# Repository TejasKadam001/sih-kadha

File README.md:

# iKwath: Smart Pod-Based Ayurvedic Decoction Appliance

**SIH26048: iKwath, a pod-based smart Kwatha (Kadha) maker that prepares a fresh, AFI/API-standardized decoction from coarse powder (yavakuta churna) on demand, in the shortest practical time, without altering the decoction's quality or yield**
Ministry of Ayush / All India Institute of Ayurveda (AIIA) | Smart India Hackathon 2026
**Team:** MACH 2
**Design philosophy:** Classical Fidelity | Hardware-Enforced Safety | Measured Endpoints, Not Timers | Honest Project Status

[-lightgrey.svg?style=flat-square)](website/)

---

## 1. Problem Statement Context (SIH26048)

Kwatha (also Kashaya or Kadha) is the primary aqueous decoction in Ayurveda. Coarse herbal powder (yavakuta churna) is boiled in a specified multiple of water and reduced, classically to one quarter of the volume, then filtered immediately.

The difficulty is that a classical Kwatha has no preservatives and stays therapeutically useful for only a few hours. Making it properly means 45 to 60 minutes of monitored simmering, so patients and OPD clinics often switch to bottled, industrially preserved syrups that suffer thermal degradation or inconsistent yield.

* **Long manual process:** open-pot evaporation needs constant attention for close to an hour.
* **Temperature ceiling:** classical practice prescribes gentle heat (Manda Agni). At or above 100 C volatile terpenes and thermolabile glycosides degrade.
* **Standardization gap:** hand preparation varies in water ratio, reduction and filtration, so dose consistency is poor.
* **No traceability:** there is no record of what was brewed, from which batch, at what concentration.

---

## 2. Integrated Solution Overview

**iKwath** is a countertop, single-dose extraction appliance built around five ideas:

1. **Pod-based dosing:** a single-use pod holds 25 to 35 g of certified coarse powder and doubles as the filter (150 to 250 micron mesh). An NTAG213 NFC tag on the rim carries the formulation profile.
2. **Vacuum-assisted evaporation:** the sealed SS304 chamber runs at 0.5 to 0.6 atm so water boils at about 82 to 86 C. The liquid boils vigorously while staying inside the 85 to 90 C envelope.
3. **Measured endpoint:** a load cell tracks the mass of the chamber and ends the boil when 300 g (+/- 2 g) has evaporated, an exact 4:1 reduction of 400 mL. The endpoint is a measurement, not a timer.
4. **Three independent hardware safety layers:** fuse, lid interlock and bimetallic thermal cutoff, all working with the firmware switched off.
5. **Companion app and cloud model:** live brew dashboard, pod profile catalogue, dose log and clinic fleet view (see the status note in section 8).

> Scientific and engineering classification: iKwath is a prototype design for a standardized decoction appliance. It is not a certified medical device, and this repository does not contain laboratory validation of extract quality. See section 10 for what is and is not built.

---

## 3. Extraction Physics

The Ayurvedic Formulary of India (AFI) and Ayurvedic Pharmacopoeia of India (API) set water ratio by herb hardness:

| Herb class | Parts | Water ratio (w/w) | Reduction | Concentration |
|---|---|---|---|---|
| Soft (Mridu): leaves, flowers | 16 | 16 | to 1/4 | about 4x |
| Medium (Madhyama): bark, stems | 8 | 8 | to 1/4 | about 2x |
| Hard (Kathina): roots, heartwood | 4 | 4 | to 1/4 | about 1x |

The working profile is 400 mL of water reduced to a 100 mL dose.

Cycle time falls from 45 to 60 minutes to 9 to 12 minutes without raising liquid temperature, using four levers:

```mermaid
graph TD
    A[Classical bottleneck] --> B[Open pot at 98-100 C]
    B --> C[Slow evaporation: 45-60 min]
    B --> D[Thermal loss of volatile actives]

    E[iKwath approach] --> F[Sealed chamber at 0.5-0.6 atm]
    F --> G[Boils at 82-86 C, Manda Agni preserved]
    E --> H[Wide shallow pan: about 3x surface area]
    E --> I[Recirculation over the pod bed]
    E --> J[Forced vapor exhaust]

    G --> K[Active cycle target: 9-12 min]
    H --> K
    I --> K
    J --> K
```

Particle size follows PCIM&H specification AFI/2020/KC/1.0: 100 percent through IS sieve 22 (710 micron) and not more than 10 percent through sieve 44 (355 micron). Details: [docs/pod-and-extraction.md](docs/pod-and-extraction.md).

---

## 4. Machine Working Principle

```mermaid
stateDiagram-v2
    [*] --> Idle: Powered on
    Idle --> PodDetect: Pod inserted, lid latched
    PodDetect --> WaterFill: NFC profile validated
    WaterFill --> PreSoak: 400 mL metered by load cell
    PreSoak --> ActiveBoil: 180 s soak finished

    state ActiveBoil {
        [*] --> PressureRamp: Vacuum pump on
        PressureRamp --> PIDHold: 0.5-0.6 atm reached
        PIDHold --> PIDHold: Temperature held 85-88 C
        PIDHold --> MassCheck: Recirculation running
        MassCheck --> [*]: 300 g evaporated
    }

    ActiveBoil --> Dispense: Vent chamber, run dispense pump
    Dispense --> Eject: about 100 mL delivered
    Eject --> Idle: Pod dropped to bin
```

Eight steps: interlocked pod loading, metered water intake, pre-soak, controlled vacuum boil, recirculation with vapor stripping, mass-reduction endpoint, filtered dispense at 55 to 60 C, automatic pod ejection. Step-by-step detail: [docs/control-sequence.md](docs/control-sequence.md).

---

## 5. Repository Layout

```
SIH/
├── README.md                      Main specification and status
├── INSTALL.md                     How to open, run and rebuild each part
├── CHANGELOG.md                   Versioned release notes
├── PUSH_LOG.md                    What each push to the repository did
├── SIH26048_PROJECT_REPORT.md     Full technical submission report
├── ps_shortlist.md                Problem-statement shortlist and selection notes
├── app/                           Product landing site (single page, with media assets)
│   ├── index.html
│   ├── styles.css
│   ├── assets/                    Product, pod and lifestyle imagery, hero video
│   └── _assets_backup/            Unused media with a restore script
├── website/                       Interactive brew-simulator web app (HTML, CSS, JS)
│   ├── index.html
│   ├── styles.css
│   ├── app.js                     Screen state machine, extraction simulator, greetings
│   ├── manifest.json
│   └── assets/
├── pcb/                           Committed KiCad project (control and power circuitry)
│   ├── ikwath.kicad_sch
│   ├── ikwath.kicad_pcb
│   └── ikwath.kicad_pro
├── ino/                           ESP32 firmware (Arduino sketch)
│   └── ikwath_firmware/
│       ├── ikwath_firmware.ino    State machine, sensors, safety checks, serial and optional HTTP
│       ├── pins.h  config.h       Pin map and tunable settings
│       ├── pid.h  hx711_lite.h    Heater PID and load-cell reader
│       └── profile.h              Pod tag payload format
├── models/                        Process model notebook: vacuum boiling, energy budget, endpoint noise, pod tag
│   └── ikwath_process_model.ipynb
├── docs/                          Engineering documentation derived from this repository
│   ├── pod-and-extraction.md
│   ├── control-sequence.md
│   ├── pinout-and-buses.md
│   ├── safety-system.md
│   ├── pcb-status.md
│   ├── bom.md
│   ├── app-and-cloud.md
│   ├── limitations.md
│   ├── judge-qna.md
│   └── README.md
├── blehpcb/                       Local PCB generation work (gitignored)
│   ├── BOM.csv
│   ├── generate_final_kicad8.py
│   ├── ikwath-control-board/  ikwath-power-board/
│   ├── *-drc.rpt  *-erc.rpt       KiCad rule-check reports
│   └── pcbreal/                   Scripted placement, routing and stackup iterations
└── blehread/                      Local research dossiers (gitignored)
    ├── research.md  structure.md  pcb.md  app_and_website.md  names.md  open.md
```

The two gitignored folders are working material that lives only on the author's machine; see [PUSH_LOG.md](PUSH_LOG.md) for what is actually pushed.

---

## 6. Dual-PCB Hardware Architecture

The electronics are split into two boards so that sensitive analog measurement is isolated from inductive relay switching.

```mermaid
flowchart LR
    subgraph PB["Power Board"]
        AC["220V AC"] --> PS1["12V 5A AC-DC supply"]
        PS1 --> F1["5A DC fuse"]
        F1 --> V12["12V bus"]
        V12 --> BUCK["LM2596 buck to 5V"]
        V12 --> RLY["Relays 1-7: heater, vacuum pump, recirculation pump, dispense pump, inlet valve, lid lock, exhaust fan"]
    end

    subgraph CB["Control Board"]
        MCU["ESP32 DevKit V1"]
        MCU --> DS["DS18B20 liquid temperature"]
        MCU --> HX["HX711 + load cell"]
        MCU --> NFC["MFRC522 NFC reader"]
        MCU --> I2C["I2C bus"]
        I2C --> OLED["SSD1306 OLED"]
        I2C --> BMP["BMP280 pressure"]
        I2C --> PCF["PCF8574 x2: relays, LEDs"]
        MCU --> TDS["Analog TDS sensor"]
        MCU --> SW["Limit switches: lid, boil-over, level"]
        MCU --> SRV["SG90 pod ejector"]
    end

    BUCK -->|5V| MCU
    PB <-->|"Ribbon: power, I2C, PID, signals"| CB
```

| Board | Target size | Notes |
|---|---|---|
| Control | 70 x 60 mm in the specification (generated variants are larger, see [docs/pcb-status.md](docs/pcb-status.md)) | 2-layer, dedicated analog ground zone, 4x M3 |
| Power | 80 x 70 mm in the specification | 2-layer, heavy power traces, opto-isolated relay drive, 4x M3 |

Pin map and I2C addresses: [docs/pinout-and-buses.md](docs/pinout-and-buses.md).

---

## 7. Three-Tier Hardware Safety System

These layers act independently of firmware:

1. **Bimetallic thermal cutoff (95 to 100 C)**, in contact with the boiler wall and in series between Relay 1 and the heater. If the chamber overheats for any reason, including a welded relay, it opens the circuit.
2. **Mechanical lid interlock**, wired in series with the heater's 12 V feed. Opening the lid cuts heater power in hardware.
3. **5 A fast-acting fuse** on the 12 V rail against short circuits and pump stall.

The firmware in `ino/` adds supervisory checks on top (boil-over sensor, water level, enclosure NTC, over-temperature, timeouts); it is a first draft that has not yet run on the appliance (section 10). Details: [docs/safety-system.md](docs/safety-system.md).

---

## 8. Companion Applications

Two web front ends are in the repository. Both run with no build step and no dependencies.

| Folder | What it is |
|---|---|
| `website/` | Interactive mobile-style app: logo intro, login, time-based greeting, pod dropdown (Triphala, Ayush, Dashamoola), five-stage extraction simulator with live countdown, temperature dial, 400 to 100 mL gauge and a PID curve pinned to the 85 to 90 C band, notification bell, pod scanner viewfinder, profile view, Android frame toggle |
| `app/` | Single-page product site: appliance, pods, app, formulations, science and standards sections, sign-in and sign-up modals, product photography and hero video |

**Status:** the extraction screen is a simulator driven by `website/app.js`. It does not connect to a device. The BLE provisioning, local WebSocket, MQTT telemetry and cloud database described in [docs/app-and-cloud.md](docs/app-and-cloud.md) are the intended architecture, not running code.

---

## 9. Bill of Materials

`blehpcb/BOM.csv` lists 46 line items (ESP32, sensors, NFC reader, display, expanders, 7 relays, pumps, valves, heater, servo, fan, safety parts, passives and connectors). The file's own total row, and the sum of its cost column, is **INR 4,588** (about US$55), reading each figure as a line total. If those were unit prices the bill would be INR 8,335, so spot-check a few lines against supplier listings before quoting a cost. Full table and notes: [docs/bom.md](docs/bom.md).

---

## 10. Project Status: Built Versus Designed

| Area | Status |
|---|---|
| Problem analysis, extraction physics, pod design | Written (`blehread/research.md`, `docs/pod-and-extraction.md`) |
| Pin-by-pin hardware specification | Written (`blehread/pcb.md`, `docs/pinout-and-buses.md`) |
| KiCad schematic and PCB | Present in several iterations; `pcb/` is the committed one. Rule-check results vary by iteration, and copper routing is incomplete in some (see [docs/pcb-status.md](docs/pcb-status.md)) |
| Web front ends | Built and runnable; extraction is simulated |
| ESP32 firmware | Written (`ino/`): full cycle, safety checks, serial and optional HTTP interface. Not yet compiled here or run on hardware |
| Physical prototype and lab validation | **Not done** (no measured extract quality, no measured cycle time) |
| Mobile app, cloud backend, MQTT | **Design only** |

The 9 to 12 minute cycle, the 85 to 90 C envelope and the 300 g endpoint are design targets derived from the physics, not measured results. An energy balance in `models/ikwath_process_model.ipynb` shows that the cycle time is set by heater power: the 50 W element in the current bill of materials is far too small for a 12 minute cycle, so the heater is an open design decision. [docs/limitations.md](docs/limitations.md) lists what is needed to turn each into a measured claim.

---

## 11. Documentation Map

| Document | Contents |
|---|---|
| [SIH26048_PROJECT_REPORT.md](SIH26048_PROJECT_REPORT.md) | Full technical submission report |
| [INSTALL.md](INSTALL.md) | Run the web apps, open the PCB, regenerate boards |
| [CHANGELOG.md](CHANGELOG.md) | Versioned release notes |
| [PUSH_LOG.md](PUSH_LOG.md) | What each push did |
| [ino/README.md](ino/README.md) | Firmware structure, cycle, safety checks, serial commands |
| [docs/](docs/README.md) | Engineering documentation set |

---

## 12. Authoritative Standards and Citations

* PCIM&H, *AFI/2020/KC/1.0: Formulary Specification of AYUSH Kvatha Churna*, Ghaziabad.
* PCIM&H, *API-2/2020/KC/1.0: Pharmacopoeial Monograph of AYUSH Kvatha Churna*, Ministry of Ayush.
* *The Ayurvedic Pharmacopoeia of India*, Parts I and II, First Edition, Ministry of Health and Family Welfare / Ministry of Ayush.
* All India Institute of Ayurveda (AIIA): guidance on quality control, good dispensing practice and clinical standardization of extemporaneous decoctions.

---

*iKwath, Smart India Hackathon 2026, Ministry of Ayush / AIIA*
*Team: MACH 2*

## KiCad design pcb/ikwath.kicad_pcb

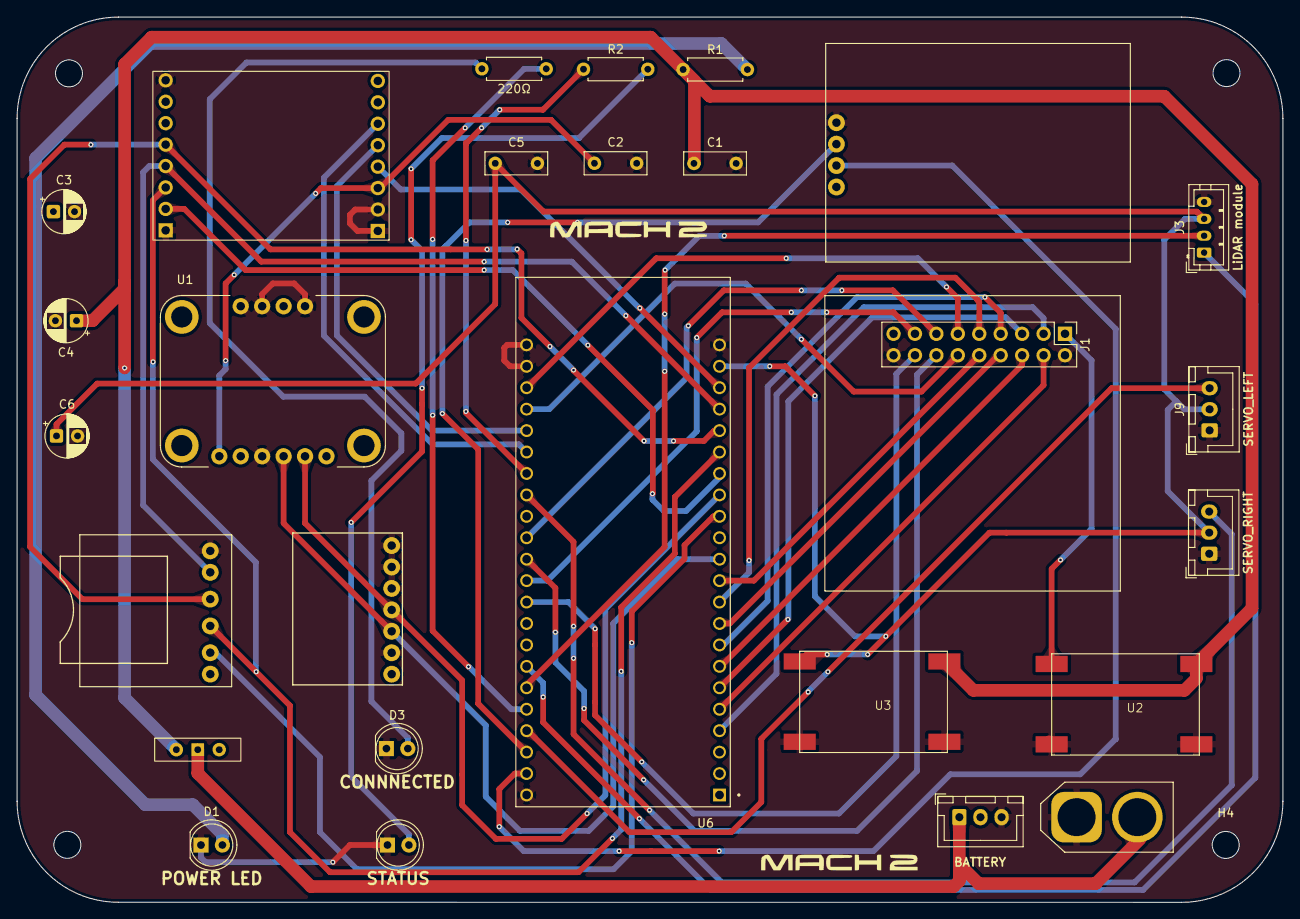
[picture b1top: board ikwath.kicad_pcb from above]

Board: 2 copper layers, 150.0 x 104.9 mm, 31 parts (0 on the bottom side), 40 nets.

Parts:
220Ω: 220Ω; R_Axial_DIN0207_L6.3mm_D2.5mm_P7.62mm_Horizontal
C1, C2, C5: 0.1µF; C_Rect_L7.2mm_W2.5mm_P5.00mm_FKS2_FKP2_MKS2_MKP2
C3, C6: 220; CP_Radial_D5.0mm_P2.50mm
C4: 470; CP_Radial_D5.0mm_P2.50mm
D1: POWER LED; LED_D5.0mm
D2: STATUS; LED_D5.0mm
D3: CONNNECTED; LED_D5.0mm
GPS1: NEO_GPS
H1, H2, H4, H6: MountingHole; MountingHole_3.2mm_M3_ISO7380
J1: CAMERA MODULE; PinHeader_2x09_P2.54mm_Vertical
J2: BATTERY; JST_XH_B3B-XH-A_1x03_P2.50mm_Vertical
J3: LiDAR module; JST_PH_B4B-PH-K_1x04_P2.00mm_Vertical
J5: XT-60; AMASS_XT60-M_1x02_P7.20mm_Vertical
J9: SERVO_LEFT; JST_XH_B3B-XH-A_1x03_P2.50mm_Vertical
J11: SERVO_RIGHT; JST_XH_B3B-XH-A_1x03_P2.50mm_Vertical
R1: 3.3KΩ; R_Axial_DIN0207_L6.3mm_D2.5mm_P7.62mm_Horizontal
R2: 220Ω; R_Axial_DIN0207_L6.3mm_D2.5mm_P7.62mm_Horizontal
SDMODULE1: sd_card_module
SW1: SW_Wuerth_450301014042; SW_Slide-03_Wuerth-WS-SLTV_10x2.5x6.4_P2.54mm
U1: BNO055; MODULE_2472
U2, U3: LM2596_buck_conv
U5: LORA_MODULE; SX1278 LoRa Module
U6: ESP32-S3-DEVKITC-1U-N8R2; XCVR_ESP32-S3-DEVKITC-1U-N8R2
m1: MS5611; MS5611F

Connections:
3.3V: C2.1, C3.1, GPS1.3V3, J1.1, SDMODULE1.3V3, U1.1 (VIN), U2.3 (VOUT+), U5.16 (VCC), m1.3.3V
5V: C5.1, C6.1, J3.3, J9.2, J11.2, U3.3 (VOUT+), U6.J1_21 (5V0)
GND: C1.2, C2.2, C3.2, C4.2, C5.2, C6.2, D1.1 (K), D2.1 (K), D3.1 (K), GPS1.GND, J1.2, J1.18, J2.3, J3.4, J5.1, J9.1, J11.1, SDMODULE1.GND, U1.3 (GND), U1.7 (ADR), U1.9 (PS1), U1.10 (PS0), U2.2 (VIN-), U2.4 (VOUT-), U3.2 (VIN-), U3.4 (VOUT-), U5.1 (GND), U5.13 (GND), U5.14 (GND), U5.15 (GND), U6.J1_22 (GND), U6.J3_1 (GND), U6.J3_21 (GND), U6.J3_22 (GND), m1.CSB, m1.GND, m1.PS, m1.SDO
GPIO1: J9.3, U6.J3_4 (GPIO1)
GPIO2: 220Ω.1, U6.J3_5 (GPIO2)
GPIO4: J1.3, U6.J1_4 (GPIO4)
GPIO5: J1.4, U6.J1_5 (GPIO5)
GPIO6: J1.5, U6.J1_6 (GPIO6)
GPIO7: J1.6, U6.J1_7 (GPIO7)
GPIO8: U1.4 (SDA), U6.J1_12 (GPIO8), m1.SCL
GPIO9: U1.5 (SCL), U6.J1_15 (GPIO9), m1.SDA
GPIO10: U5.5 (NSS), U6.J1_16 (GPIO10)
GPIO11: SDMODULE1.MOSI, U5.3 (MOSI), U6.J1_17 (GPIO11)
GPIO12: SDMODULE1.CLK, U5.4 (SCK), U6.J1_18 (GPIO12)
GPIO13: SDMODULE1.MISO, U5.2 (MISO), U6.J1_19 (GPIO13)
GPIO14: U5.6 (RESET), U6.J1_20 (GPIO14)
GPIO15: J1.7, U6.J1_8 (GPIO15)
GPIO16: J1.8, U6.J1_9 (GPIO16)
GPIO17: J1.9, U6.J1_10 (GPIO17)
GPIO18: J1.10, U6.J1_11 (GPIO18)
GPIO19: J1.11, U6.J3_20 (USB_D-/GPIO19)
GPIO20: J1.12, U6.J3_19 (USB_D+/GPIO20)
GPIO21: U5.7 (DI0O), U6.J3_18 (GPIO21)
GPIO35: J1.13, U6.J3_13 (GPIO35)
GPIO36: J1.14, U6.J3_12 (GPIO36)
GPIO37: J1.15, U6.J3_11 (GPIO37)
GPIO38: J1.16, U6.J3_10 (GPIO38)
GPIO41: J3.1, U6.J3_7 (MTDI/GPIO41)
GPIO42: J3.2, U6.J3_6 (MTMS/GPIO42)
GPIO43: GPS1.RX, U6.J3_2 (U0TXD/GPIO43)
GPIO44: GPS1.TX, U6.J3_3 (U0RXD/GPIO44)
GPIO45: J11.3, U6.J3_15 (GPIO45)
GPIO46: SDMODULE1.CS, U6.J1_14 (GPIO46)
GPIO47: U5.8 (DIO1), U6.J3_17 (GPIO47)
GPIO48: R2.1, U6.J3_16 (GPIO48)
unnamed: D1.2 (A), R1.2
unnamed: D2.2 (A), R2.2
unnamed: 220Ω.2, D3.2 (A)
unnamed: J2.1, J5.2, SW1.1 (B)
VIN: C1.1, C4.1, R1.1, SW1.2 (C), U2.1 (VIN+), U3.1 (VIN+)
